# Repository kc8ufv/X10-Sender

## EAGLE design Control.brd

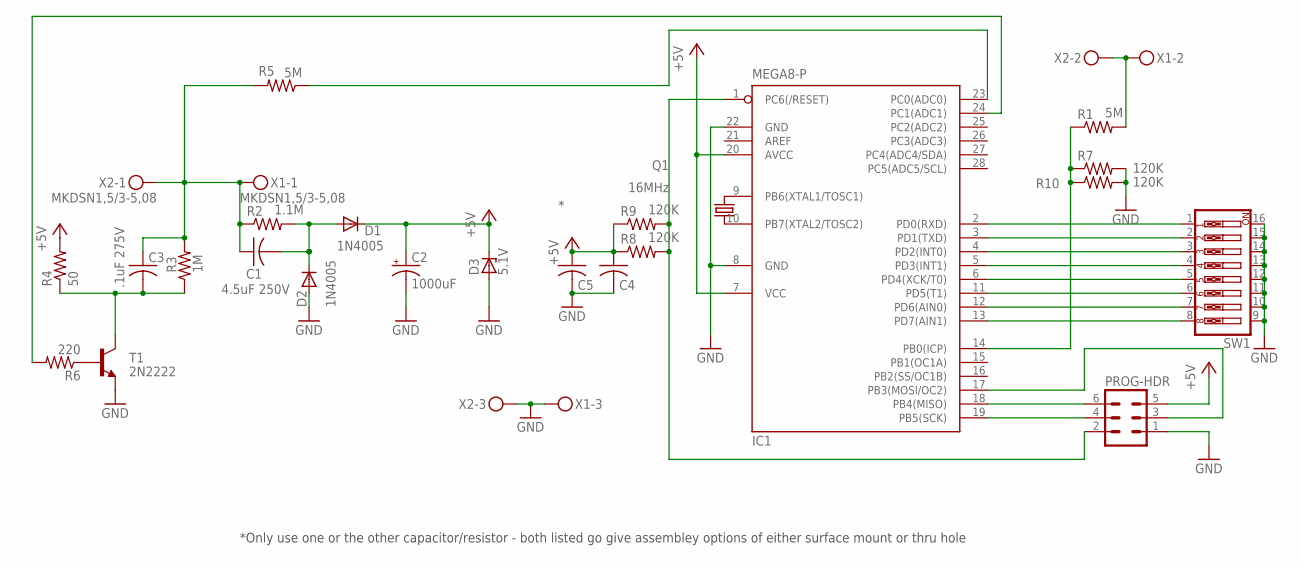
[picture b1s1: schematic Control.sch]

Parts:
C1: 4.5uF 250V; C275-205X316
C2: 1000uF; E5-13
C3: .1uF 275V; C150-091X182
C4: C-US025-024X044; C025-024X044
C5: C-USC0402K; C0402K
D1, D2: 1N4005; DO41-10
D3: 5.1V; DO34Z7
IC1: MEGA8-P; DIL28-3
PROG-HDR: MA03-2
Q1: 16MHz; TC38H
R1: 5M; 0414/15
R2: 1.1M; 0414/15
R3: 1M; 0411/12
R4: 50; 0309/12
R5: 5M; 0411/12
R6: 220; 0411/12
R7, R8: 120K; 0207/7
R9, R10: 120K; M0805
SW1: SW_DIP-8; EDG-08
T1: 2N2222; TO92
X1, X2: MKDSN1,5/3-5,08

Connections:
+5V: C2.+, C4.1, C5.1, D1.C, D3.C, IC1.7 (VCC), IC1.20 (AVCC), PROG-HDR.5, R4.2, R8.1, R9.1
GND: C2.-, C4.2, C5.2, D2.A, D3.A, IC1.8 (GND), IC1.22 (GND), PROG-HDR.1, R7.2, R10.2, SW1.9, SW1.10, SW1.11, SW1.12, SW1.13, SW1.14, SW1.15, SW1.16, T1.1 (E), X1.3, X2.3
unnamed: R1.2, X1.2, X2.2
unnamed: C1.1, C3.1, R2.1, R3.2, R5.2, X1.1, X2.1
unnamed: C1.2, D1.A, D2.C, R2.2
unnamed: R6.1, T1.2 (B)
unnamed: IC1.18 (PB4(MISO)), PROG-HDR.6
unnamed: IC1.19 (PB5(SCK)), PROG-HDR.4
unnamed: IC1.1 (PC6(/RESET)), PROG-HDR.2, R8.2, R9.2
unnamed: IC1.17 (PB3(MOSI/OC2)), PROG-HDR.3
unnamed: IC1.2 (PD0(RXD)), SW1.1
unnamed: IC1.3 (PD1(TXD)), SW1.2
unnamed: IC1.4 (PD2(INT0)), SW1.3
unnamed: IC1.5 (PD3(INT1)), SW1.4
unnamed: IC1.6 (PD4(XCK/T0)), SW1.5
unnamed: IC1.11 (PD5(T1)), SW1.6
unnamed: IC1.12 (PD6(AIN0)), SW1.7
unnamed: IC1.13 (PD7(AIN1)), SW1.8
unnamed: IC1.14 (PB0(ICP)), R1.1, R7.1, R10.1
unnamed: C3.2, R3.1, R4.1, T1.3 (C)
unnamed: IC1.9 (PB6(XTAL1/TOSC1)), Q1.2
unnamed: IC1.23 (PC0(ADC0)), R5.1
unnamed: IC1.24 (PC1(ADC1)), R6.2
unnamed: IC1.10 (PB7(XTAL2/TOSC2)), Q1.1

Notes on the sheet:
*Only use one or the other capacitor/resistor - both listed go give assembley options of either surface mount or thru hole

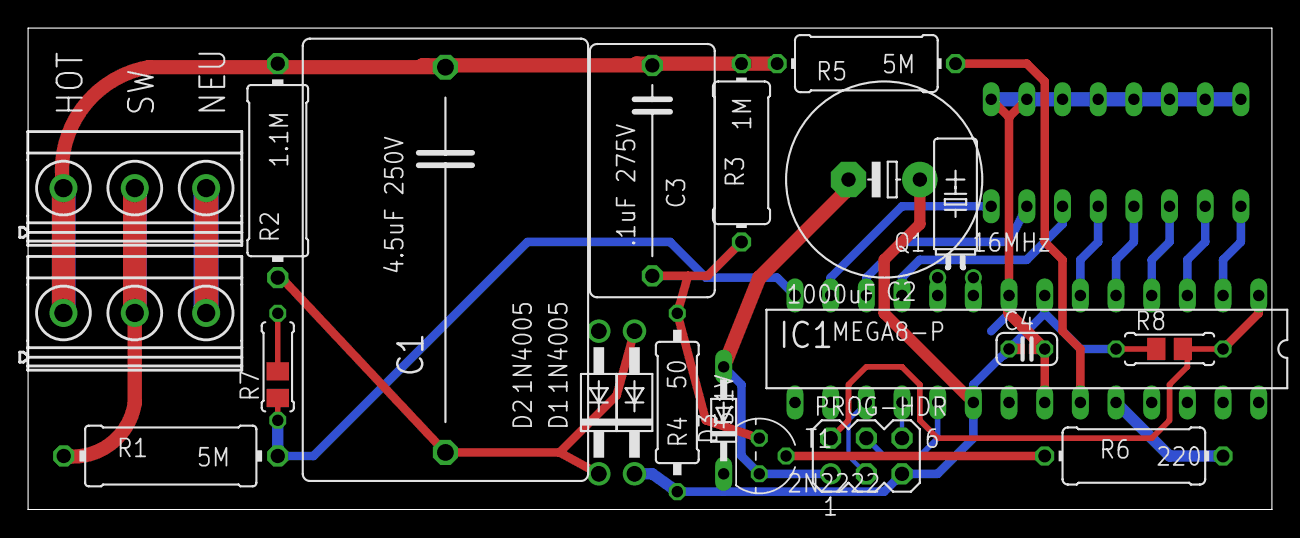
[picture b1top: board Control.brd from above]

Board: 2 copper layers, 88.6 x 34.3 mm, 25 parts (1 on the bottom side), 24 nets.

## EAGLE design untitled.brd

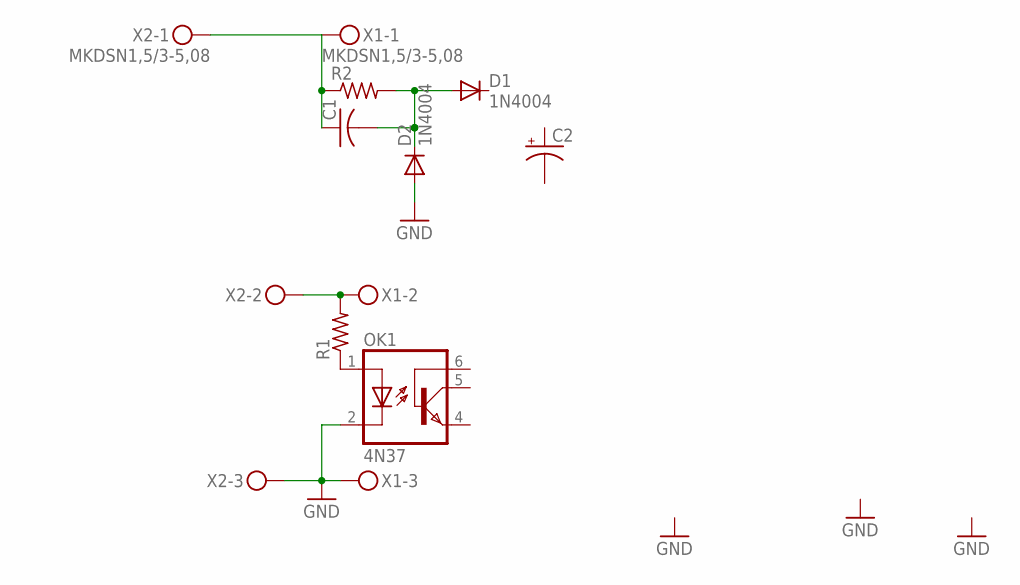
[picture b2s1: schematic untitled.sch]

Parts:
C1: C-US275-205X316; C275-205X316
C2: CPOL-USE5-13; E5-13
D1, D2: 1N4004; DO41-10
OK1: 4N37; DIL06
R1, R2: R-US_0617/5V; 0617V
X1, X2: MKDSN1,5/3-5,08

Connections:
GND: D2.A, OK1.2 (C), X1.3, X2.3
unnamed: R1.2, X1.2, X2.2
unnamed: OK1.1 (A), R1.1
unnamed: C1.1, R2.1, X1.1, X2.1
unnamed: C1.2, D1.A, D2.C, R2.2

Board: 2 copper layers, 9 parts (0 on the bottom side), 5 nets, no tracks yet.

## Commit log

2019-09-23 Add all files to Git
2019-09-23 updated schematic and board
2019-09-23 Code cleanup, and comments added
2019-10-04 Updated schematic and board to add needed pullup resistor to reset pin on Atmega. Also added surface mount pads for local filter capacitor. Pullup resistor located to fit inside central channel of a 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
2019-10-04 Added Eagle project file
2019-10-04 last updated board
2019-10-06 Added surface mount options for low voltage section
2019-10-06 Updated board - relocated programming header and large filter capacitor from DC block due to assembly dificulties stacking the filter capacitor on top of the diodes.
2019-10-06 Slight board size reduction
